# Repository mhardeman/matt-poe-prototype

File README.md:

# matt-poe-prototype
This is a KiCad design containing a schematic & PCB layout for a prototype PoE (Power over Ethernet) PD (Powered Device).

It provides for output isolation between the PoE delivery and the output power rails.  It provides for both 12V and 5V output rails, with a common ground for those two rails.

This is a prototype.  I'm happy to accept issues with questions or suggestions for improvement, and would very happily review any pull requests that come in.

## Update 2026/07/09
Apparently some one(s) at [PCBWay](https://pcbway.com) saw this Github project or my post(s) about it on Reddit, because a representative from PCBWay reached out to me and offered to sponsor a run of these boards for free and even let me get a free solder stencil with the boards, all for the simple ask that I provide an honest review of the sponsored boards & stencil.  My review is: they look & feel great, and they function fantastically.  I'll be posting more -- including an assembly and testing video -- in the coming days.  In the mean time, check out the [photos of the PCBWay boards](pcbway/)  All told, PCBWay let me put together a purchase of these boards, the stencil, and some premium options, and shipping, all without cost to me.  It's wonderful to see a company serving both hobbyists and industry ALSO materially contribute!  I'm grateful.

## Detailed Description

This design utilizes the 3Peak TPE15017 and/or Monolithic Power Systems MP8017 -- they're largely interchangeable in this design, though tolerances on the 3Peak seem to be favorable, which can improve your efficiency.  This tiny IC handles the PoE power detection and classification and provides an active-clamp flyback controller with integrated low-side & clamp MOSFETs.  This part, in conjunction with an appropriate transformer provides a 12V output rail, which is further routed in this design to an inexpensive buck converter to provide for a 5V output rail.

In my testing up to this point, this design easily provides at least 10W of usable power out the 5V rail.  I've had it pulling 5V/2A on my DC test load continuously for several days.

[Bill of Materials](matt-poe-prototype.csv)

[More visuals](visuals/)

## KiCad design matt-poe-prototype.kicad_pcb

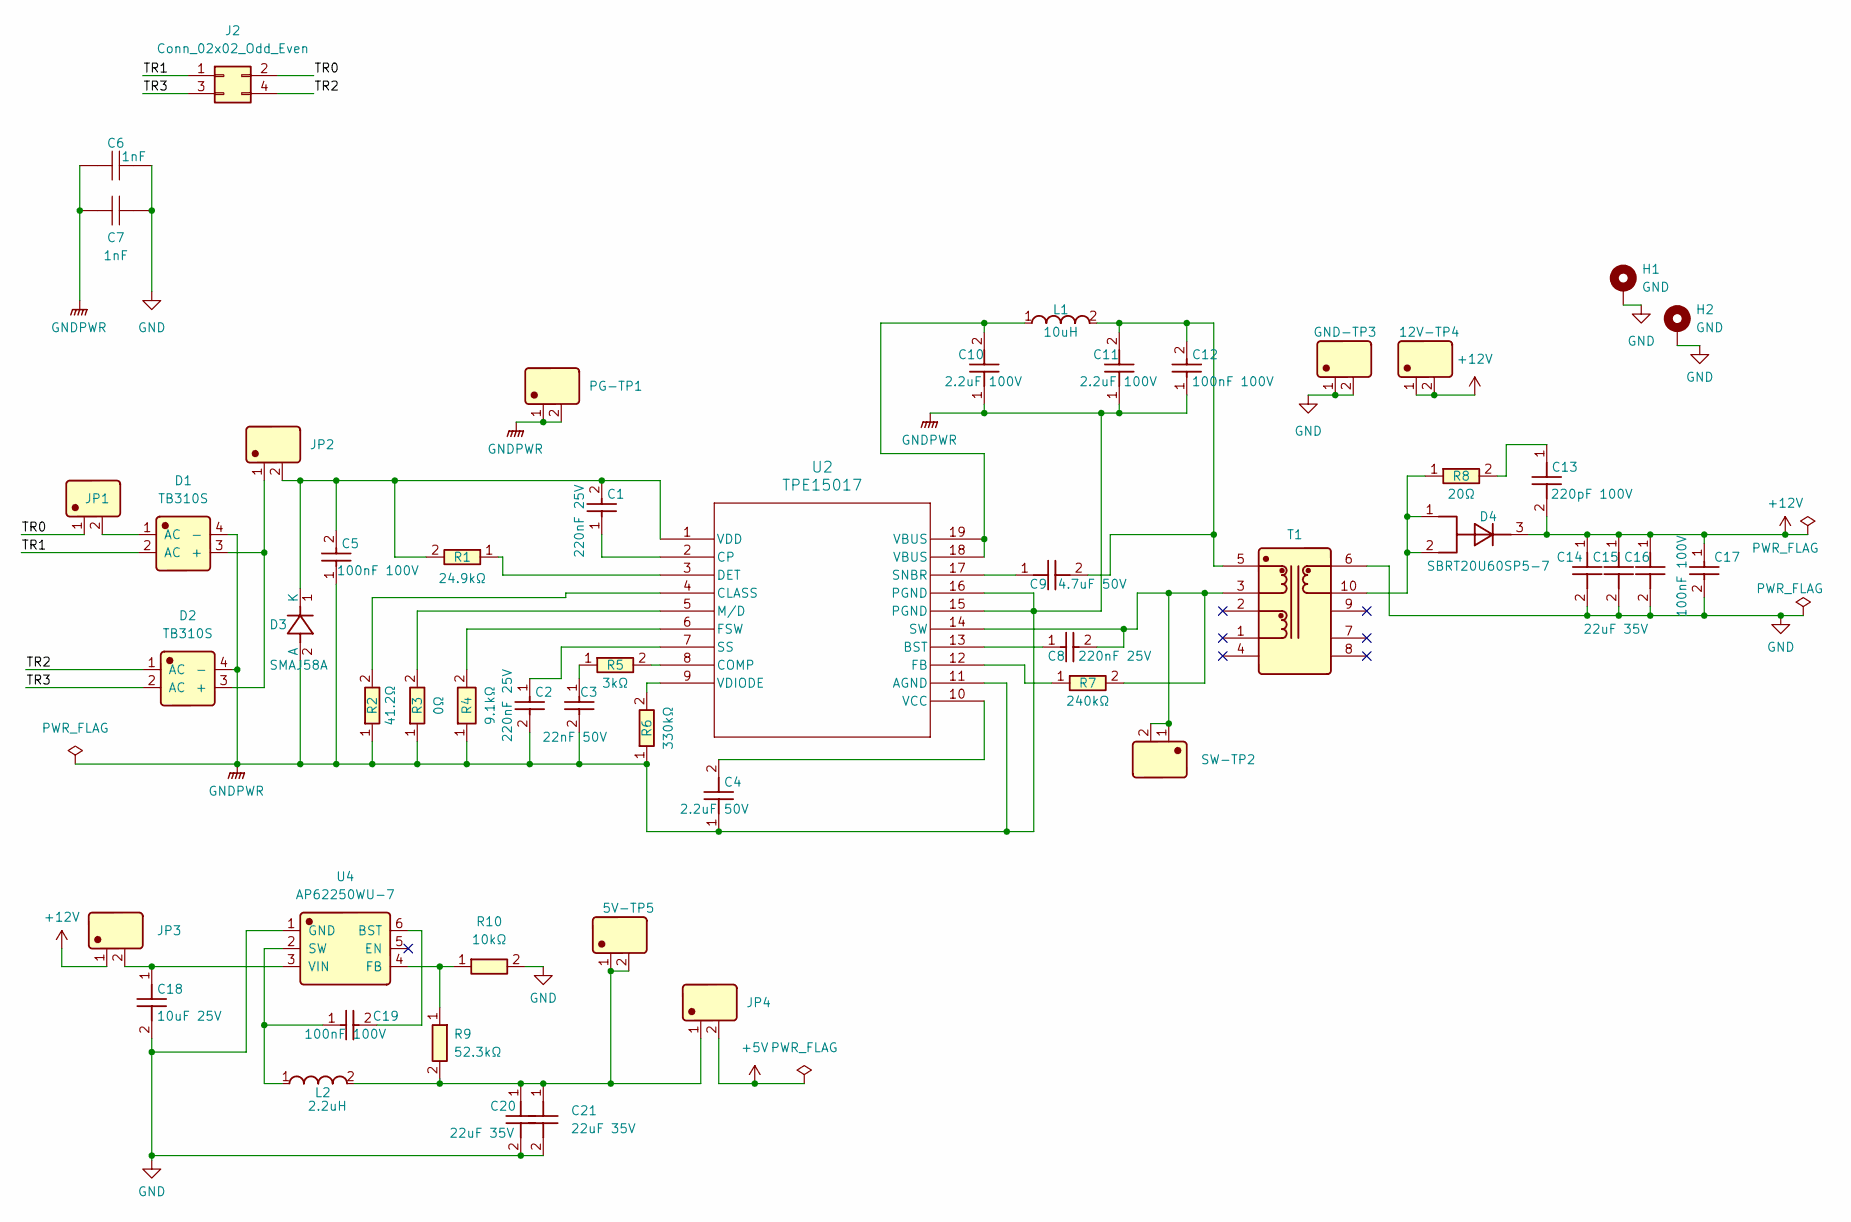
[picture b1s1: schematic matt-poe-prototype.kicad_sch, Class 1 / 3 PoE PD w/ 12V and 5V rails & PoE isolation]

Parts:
5V-TP5, 12V-TP4: PZ200V-11-02P; Manufacturer Part PZ200V-11-02P; LCSC C541856
C1, C2, C8: 220nF 25V; CL10B224KA8NNNC; Manufacturer Part CL10B224KA8NNNC; LCSC C21120
C3: 22nF 50V; C_0603_C21122; Manufacturer Part CL10B223KB8NNNC; LCSC C21122
C4: 2.2uF 50V; C_0805_C377773; Manufacturer Part CL21A225KBQNNNE; LCSC C377773
C5, C12, C17, C19: 100nF 100V; C_0805_C28233; Manufacturer Part CL21B104KCFNNNE; LCSC C28233
C6, C7: 1nF; C1808; MPN GR442QR73D102KW01L; LCSC C76916
C9: 4.7uF 50V; C_0805_C437557; Manufacturer Part GRM21BZ71H475KE15L; LCSC C437557
C10, C11: 2.2uF 100V; C_1206_C170101; Manufacturer Part CL31B225KCHSNNE; LCSC C170101
C13: 220pF 100V; GCM1885C2A221JA16D; Manufacturer Part GCM1885C2A221JA16D; LCSC C388907
C14, C15, C16, C20, C21: 22uF 35V; C_1210_C778721; Manufacturer Part GMK325BJ226MM-P; LCSC C778721
C18: 10uF 25V; GRM21BZ71E106KE15L; Manufacturer Part GRM21BZ71E106KE15L; LCSC C237493
D1, D2: TB310S; ABS_TB310S; Manufacturer Part TB310S; LCSC C382784
D3: SMAJ58A; SMAJ58A_C19077554; Manufacturer Part SMAJ58A; LCSC C19077554
D4: SBRT20U60SP5-7; Manufacturer Part SBRT20U60SP5-7; LCSC C156299
GND-TP3: PZ200V-11-02P; Manufacturer Part PZ200V-11-02P; LCSC C541856
H1, H2: GND; MountingHole_2.7mm_M2.5_Pad_TopBottom
J2: Conn_02x02_Odd_Even; PinSocket_2x02_P2.54mm_Vertical; MPN 61300421821; LCSC C2840016
JP1, JP2, JP3, JP4: PZ200V-11-02P; Manufacturer Part PZ200V-11-02P; LCSC C541856
L1: 10uH; DFE252012F-100M_P2; Manufacturer Part DFE252012F-100M=P2; LCSC C703141
L2: 2.2uH; L_1210_C18724399; Manufacturer Part FTC322510S2R2MBCA; LCSC C18724399
PG-TP1: PZ200V-11-02P; Manufacturer Part PZ200V-11-02P; LCSC C541856
R1: 24.9kΩ; R_0603_C25962; Manufacturer Part 0603WAF2492T5E; LCSC C25962
R2: 41.2Ω; R_0603_C246850; Manufacturer Part 0603WAF412JT5E; LCSC C246850
R3: 0Ω; R_0603_C21189; Manufacturer Part 0603WAF0000T5E; LCSC C21189
R4: 9.1kΩ; FRC0603J912_TS; Manufacturer Part FRC0603J912 TS; LCSC C2907210
R5: 3kΩ; R_0603_C4211; Manufacturer Part 0603WAF3001T5E; LCSC C4211
R6: 330kΩ; 0603WAF3303T5E; Manufacturer Part 0603WAF3303T5E; LCSC C23137
R7: 240kΩ; R_0603_C4197; Manufacturer Part 0603WAF2403T5E; LCSC C4197
R8: 20Ω; R_1206_C17903; Manufacturer Part RC1206FR-7W20RL; LCSC C859156
R9: 52.3kΩ; R_0805_C17740; Manufacturer Part 0805W8F5232T5E; LCSC C17740
R10: 10kΩ; R_0805_C17414; Manufacturer Part 0805W8F1002T5E; LCSC C17414
SW-TP2: PZ200V-11-02P; Manufacturer Part PZ200V-11-02P; LCSC C541856
T1: EP475SG-10; XFMR_EP13_EP475SG-10; Manufacturer Part EP475SG-10; LCSC C42401037
U2: TPE15017; QFN-19_MP8017_MNP; MPN TPE15017; LCSC C26159122
U4: AP62250WU-7; Manufacturer Part AP62250WU-7; LCSC C5184228

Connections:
+5V: JP4.2
+12V: 12V-TP4.1, 12V-TP4.2, C13.2, C14.1, C15.1, C16.1, C17.1, D4.3, JP3.1
/TR0: J2.2, JP1.1
/TR1: D1.2 (AC), J2.1
/TR2: D2.1 (AC), J2.4
/TR3: D2.2 (AC), J2.3
GND: C6.2, C7.2, C14.2, C15.2, C16.2, C17.2, C18.2, C20.2, C21.2, GND-TP3.1, GND-TP3.2, H1.1 (1_1), H2.1 (1_1), R10.2, T1.6, U4.1 (GND)
GNDPWR: C2.2, C3.2, C4.1, C5.1, C6.1, C7.1, C10.1, C11.1, C12.1, D1.4 (-), D2.4 (-), D3.2 (A), PG-TP1.1, PG-TP1.2, R2.1, R3.1, R4.1, R6.1, U2.11 (AGND), U2.15 (PGND), U2.16 (PGND)
unnamed: 5V-TP5.1, 5V-TP5.2, C20.1, C21.1, JP4.1, L2.2, R9.2
unnamed: C3.1, R5.1
unnamed: C10.2, L1.1, U2.18 (VBUS), U2.19 (VBUS)
unnamed: C9.2, C11.2, C12.2, L1.2, T1.5
unnamed: C13.1, R8.2
unnamed: D1.3 (+), D2.3 (+), JP2.1
unnamed: D1.1 (AC), JP1.2
unnamed: C1.2, C5.2, D3.1 (K), JP2.2, R1.2, U2.1 (VDD)
unnamed: D4.1, D4.2, R8.1, T1.10
unnamed: C8.1, U2.13 (BST)
unnamed: R2.2, U2.4 (CLASS)
unnamed: R5.2, U2.8 (COMP)
unnamed: C1.1, U2.2 (CP)
unnamed: R1.1, U2.3 (DET)
unnamed: R7.1, U2.12 (FB)
unnamed: R4.2, U2.6 (FSW)
unnamed: R3.2, U2.5 (M/D)
unnamed: C9.1, U2.17 (SNBR)
unnamed: C2.1, U2.7 (SS)
unnamed: C8.2, R7.2, SW-TP2.1, SW-TP2.2, T1.3, U2.14 (SW)
unnamed: C4.2, U2.10 (VCC)
unnamed: R6.2, U2.9 (VDIODE)
unnamed: C19.2, U4.6 (BST)
unnamed: R9.1, R10.1, U4.4 (FB)
unnamed: C19.1, L2.1, U4.2 (SW)
unnamed: C18.1, JP3.2, U4.3 (VIN)

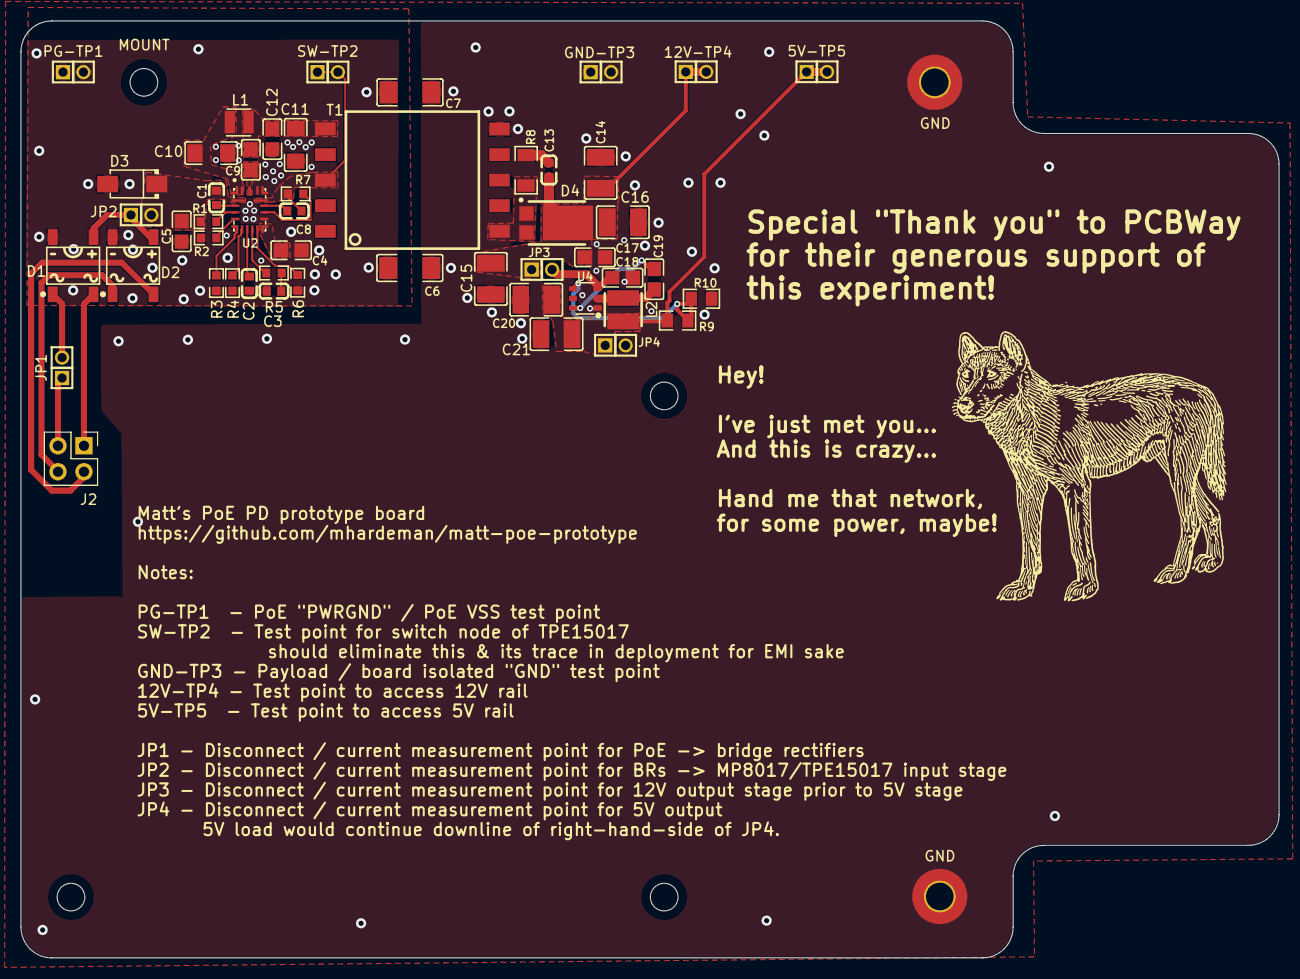
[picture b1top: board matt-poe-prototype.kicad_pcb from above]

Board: 2 copper layers, 123.0 x 91.6 mm, 56 parts (0 on the bottom side), 33 nets.

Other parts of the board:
MH2, MH3, MH4: MountingHole_2.7mm_M2.5
MOUNT: MountingHole_2.7mm_M2.5

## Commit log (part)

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2026-06-12 I would like BOM to be uploadable
2026-06-12 Initial project submission
2026-06-12 added schematic png file
2026-06-12 Update README.md
    Added schematic png to readme
2026-06-12 Adding visualization of front board design
2026-06-12 formatting
2026-06-12 Updating ignores
2026-06-13 adding some real life switch node waveforms when running under mild load
